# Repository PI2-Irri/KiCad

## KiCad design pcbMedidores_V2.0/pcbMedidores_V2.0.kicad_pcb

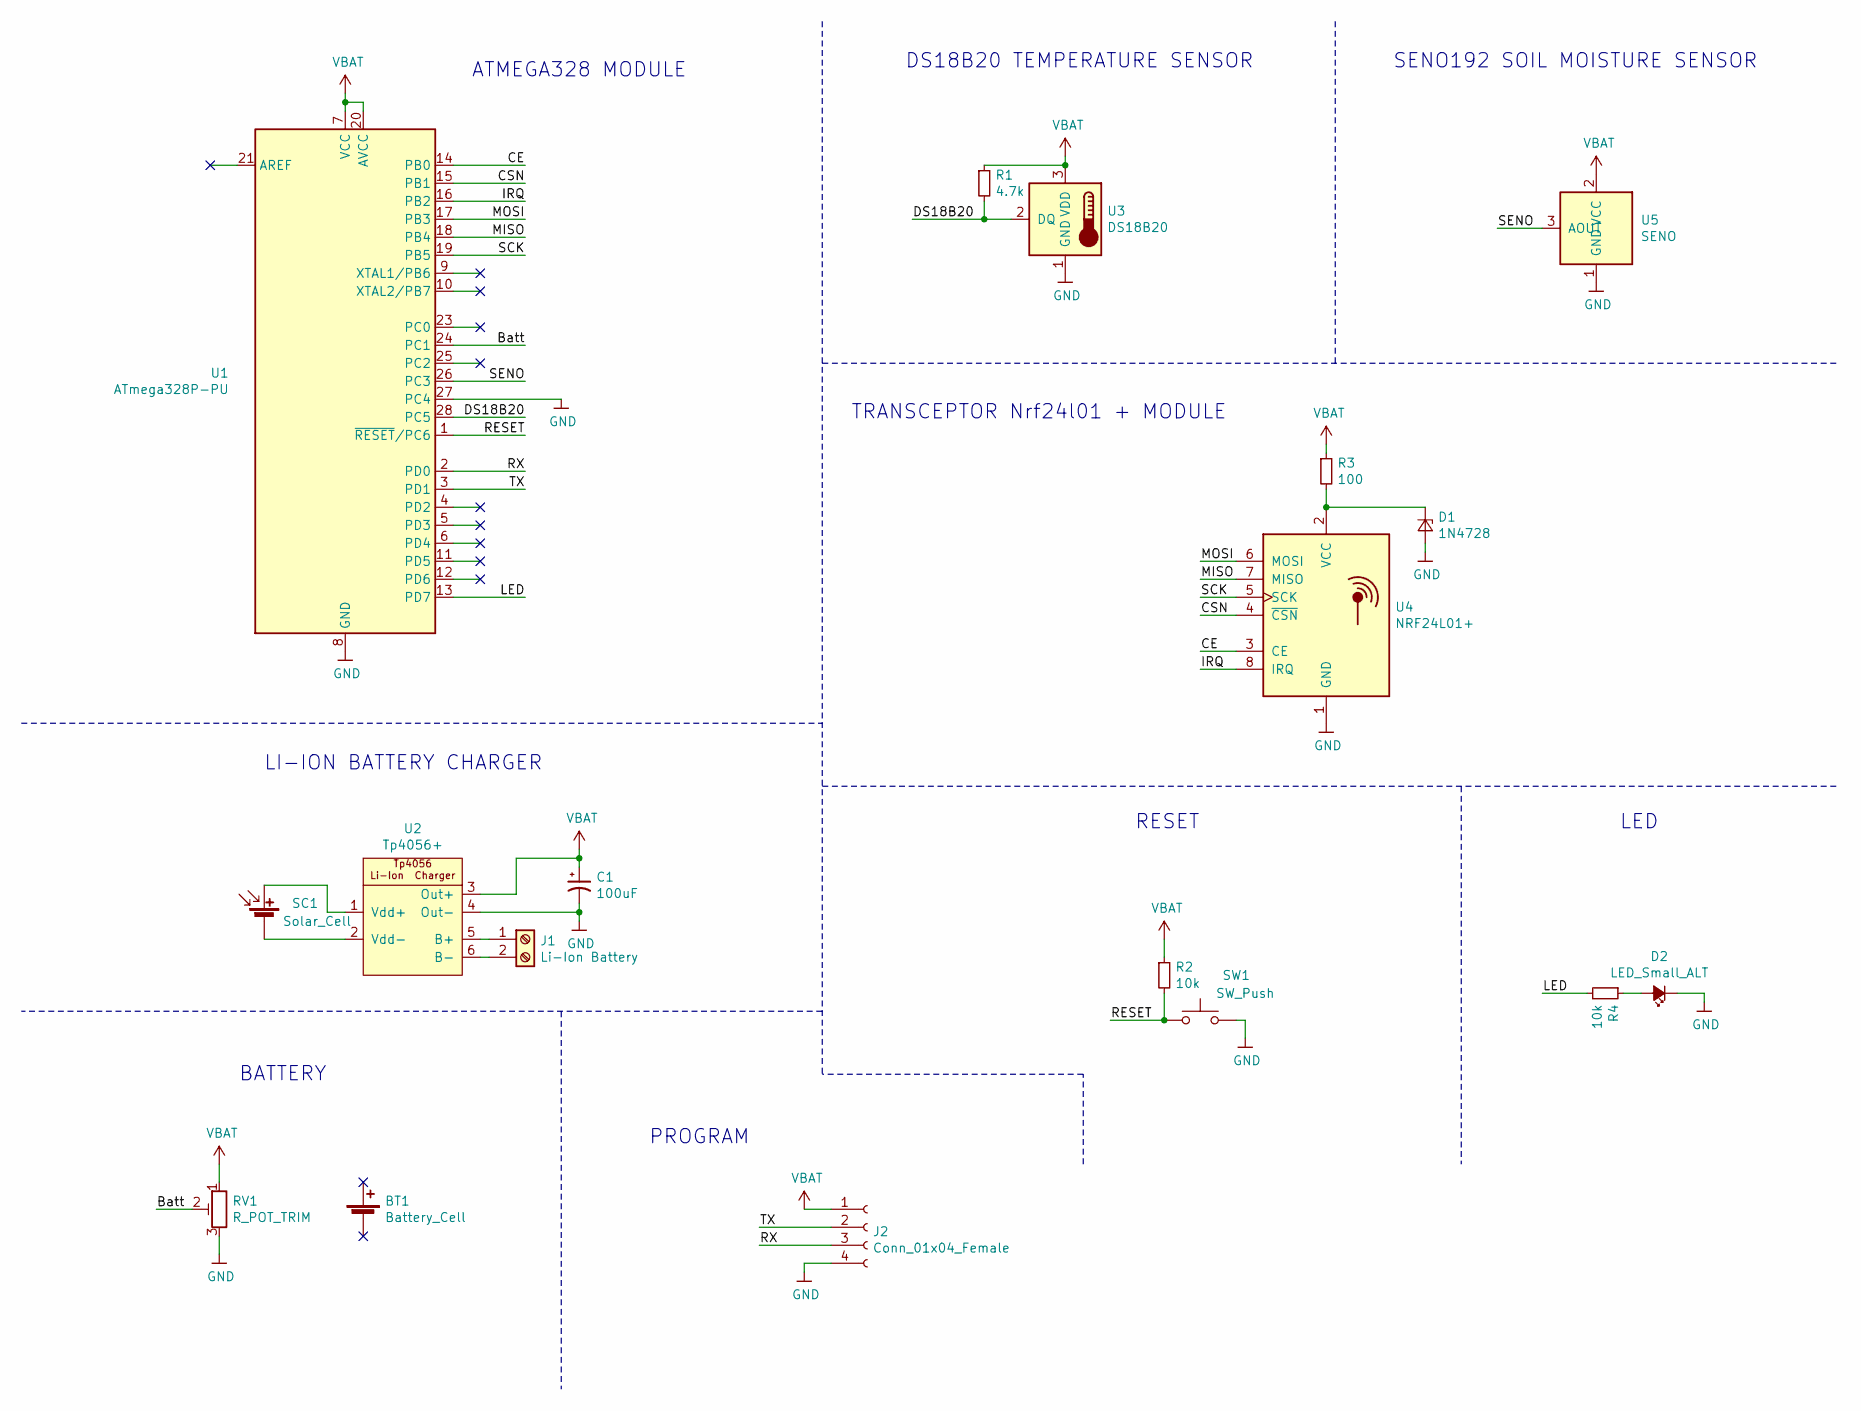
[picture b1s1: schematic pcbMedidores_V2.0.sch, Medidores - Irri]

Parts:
BT1: Battery_Cell; BatteryHolder
C1: 100uF; CP_Radial_D6.3mm_P2.50mm
D1: 1N4728; D_DO-41_SOD81_P10.16mm_Horizontal
D2: LED_Small_ALT; LED_Rectangular_W3.0mm_H2.0mm
J1: Li-Ion Battery; TerminalBlock_bornier-2_P5.08mm
J2: Conn_01x04_Female; PinHeader_1x04_P2.54mm_Vertical
R1: 4.7k; R_Axial_DIN0207_L6.3mm_D2.5mm_P7.62mm_Horizontal
R2, R4: 10k; R_Axial_DIN0207_L6.3mm_D2.5mm_P7.62mm_Horizontal
R3: 100; R_Axial_DIN0207_L6.3mm_D2.5mm_P7.62mm_Horizontal
RV1: R_POT_TRIM; Potentiometer_Bourns_3296W_Vertical
SC1: Solar_Cell; JST_XH_B2B-XH-A_1x02_P2.50mm_Vertical
SW1: SW_Push; SW_PUSH_6mm_H4.3mm
U1: ATmega328P-PU; DIP-28_W7.62mm_Socket_LongPads
U2: Tp4056+
U3: DS18B20; JST_XH_B3B-XH-A_1x03_P2.50mm_Vertical
U4: NRF24L01+; nRF24L01_Breakout
U5: SENO; PinHeader_1x03_P2.54mm_Vertical

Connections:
/Batt: RV1.2, U1.24 (PC1)
/CE: U1.14 (PB0), U4.3 (CE)
/CSN: U1.15 (PB1), U4.4 (~CSN)
/DS18B20: R1.2, U1.28 (PC5), U3.2 (DQ)
/IRQ: U1.16 (PB2), U4.8 (IRQ)
/LED: R4.2, U1.13 (PD7)
/MISO: U1.18 (PB4), U4.7 (MISO)
/MOSI: U1.17 (PB3), U4.6 (MOSI)
/RESET: R2.2, SW1.1, U1.1 (~RESET~/PC6)
/RX: J2.3, U1.2 (PD0)
/SCK: U1.19 (PB5), U4.5 (SCK)
/SENO: U1.26 (PC3), U5.3 (AOUT)
/TX: J2.2, U1.3 (PD1)
unnamed: D1.1 (K), R3.2, U4.2 (VCC)
unnamed: D2.2 (A), R4.1
unnamed: J1.1, U2.5 (B+)
unnamed: J1.2, U2.6 (B-)
unnamed: SC1.1 (+), U2.1 (Vdd+)
unnamed: SC1.2 (-), U2.2 (Vdd-)
VBUS: C1.1, J2.1, R1.1, R2.1, R3.1, RV1.1, U1.7 (VCC), U1.20 (AVCC), U2.3 (Out+), U3.3 (VDD), U5.2 (VCC)

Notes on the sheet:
LED
ATMEGA328 MODULE
DS18B20 TEMPERATURE SENSOR
SENO192 SOIL MOISTURE SENSOR
TRANSCEPTOR Nrf24l01 + MODULE
LI-ION BATTERY CHARGER
PROGRAM
RESET
BATTERY

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
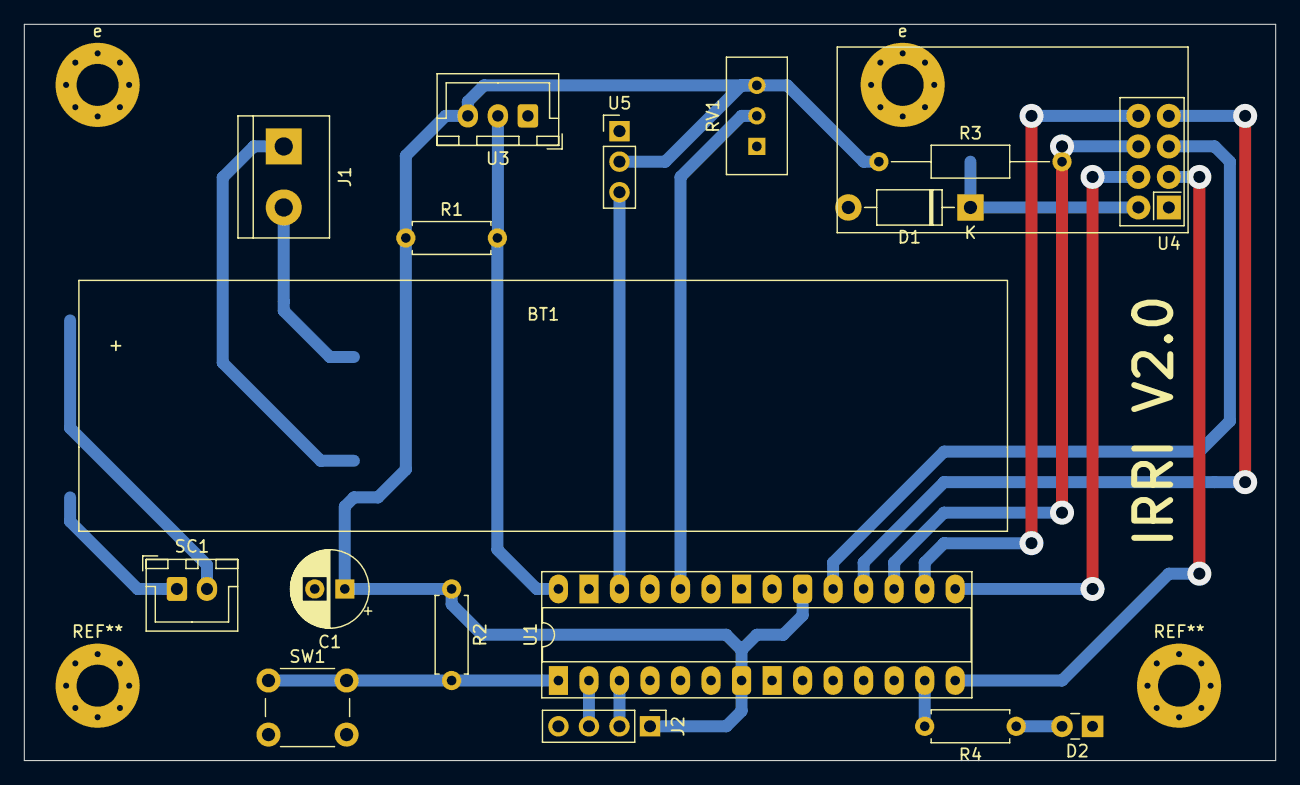
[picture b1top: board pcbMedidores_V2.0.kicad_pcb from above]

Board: 2 copper layers, 104.1 x 61.3 mm, 20 parts (1 on the bottom side), 21 nets.

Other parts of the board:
e: MountingHole_3.5mm_Pad_Via
e#2: MountingHole_3.5mm_Pad_Via

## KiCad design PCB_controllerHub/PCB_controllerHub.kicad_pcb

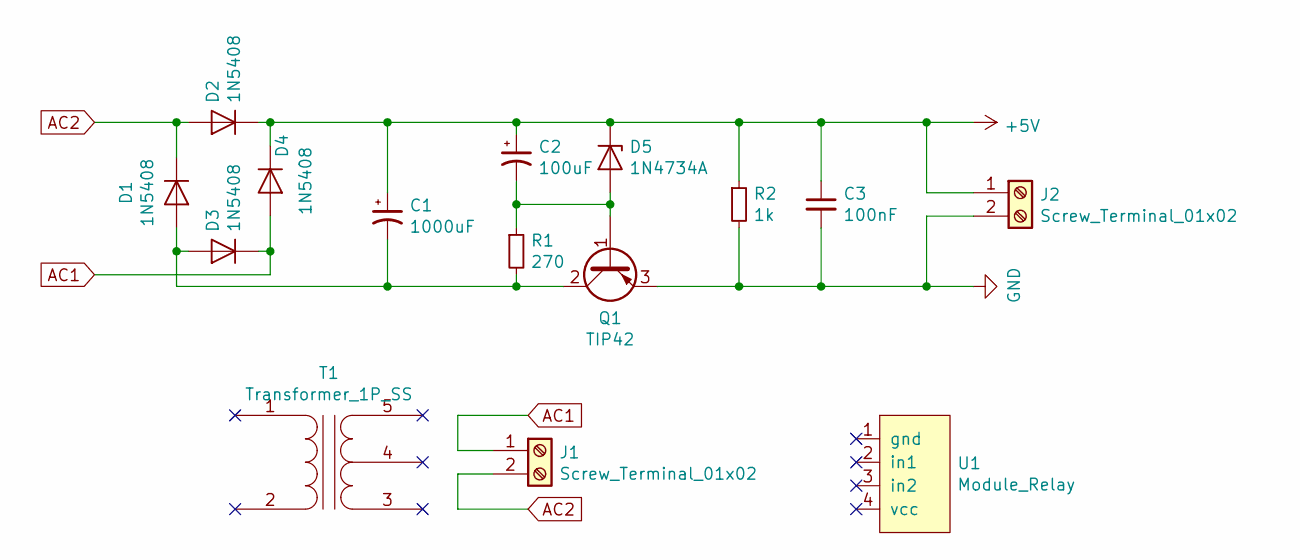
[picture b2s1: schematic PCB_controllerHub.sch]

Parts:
C1: 1000uF; CP_Radial_D10.0mm_P5.00mm
C2: 100uF; CP_Radial_D6.3mm_P2.50mm
C3: 100nF; C_Rect_L7.2mm_W2.5mm_P5.00mm_FKS2_FKP2_MKS2_MKP2
D1, D2, D3, D4: 1N5408; D_DO-201AD_P15.24mm_Horizontal
D5: 1N4734A; D_DO-41_SOD81_P10.16mm_Horizontal
J1, J2: Screw_Terminal_01x02; TerminalBlock_bornier-2_P5.08mm
Q1: TIP42; TO-220-3_Vertical
R1: 270; R_Axial_DIN0309_L9.0mm_D3.2mm_P12.70mm_Horizontal
R2: 1k; R_Axial_DIN0207_L6.3mm_D2.5mm_P10.16mm_Horizontal
T1: Transformer_1P_SS; Trafo_1A_6V
U1: Module_Relay; Module_relay

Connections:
+5V: C1.1, C2.1, C3.1, D2.1 (K), D4.1 (K), D5.1 (K), J2.1, R2.1
AC1: D3.1 (K), D4.2 (A), J1.1
AC2: D1.1 (K), D2.2 (A), J1.2
GND: C3.2, J2.2, Q1.3 (E), R2.2
unnamed: C1.2, D1.2 (A), D3.2 (A), Q1.2 (C), R1.2
unnamed: C2.2, D5.2 (A), Q1.1 (B), R1.1

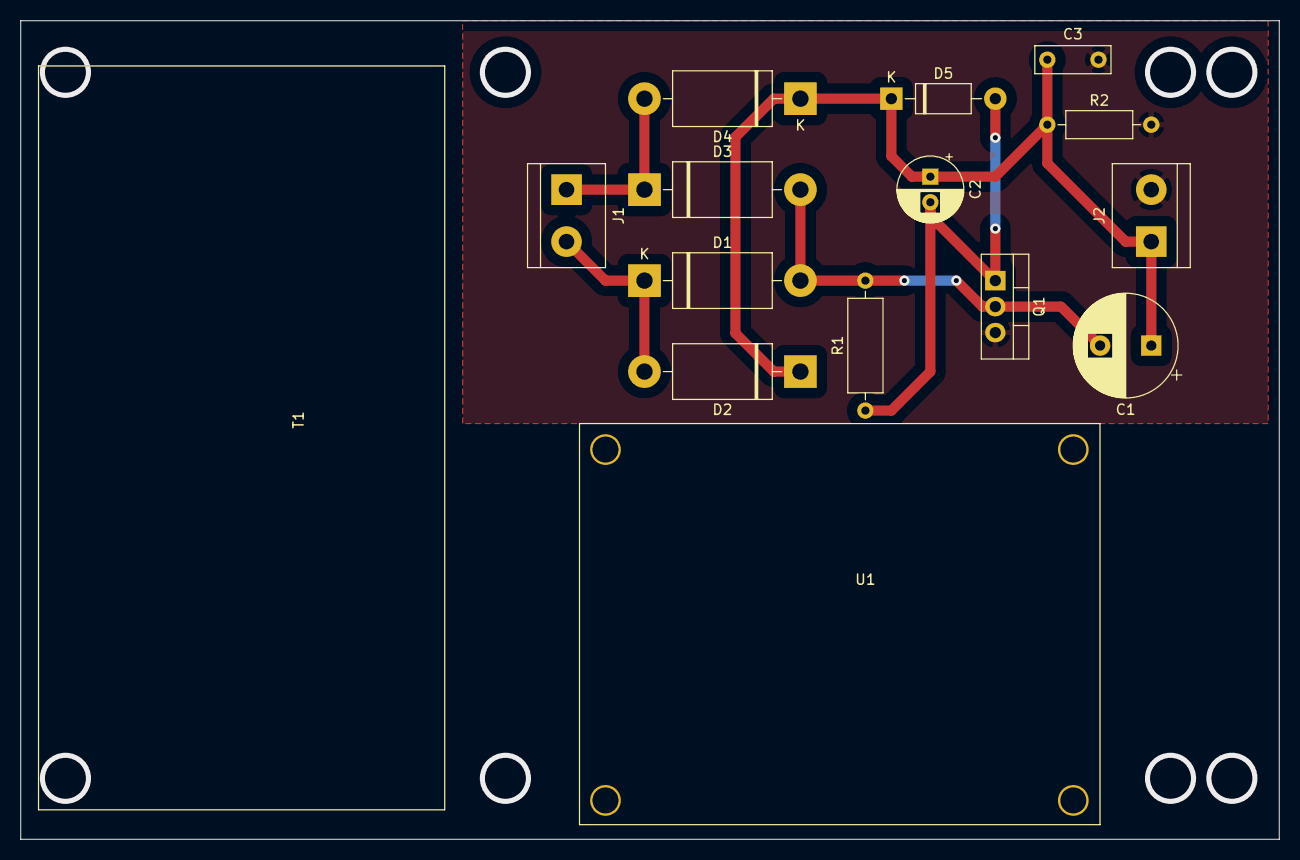
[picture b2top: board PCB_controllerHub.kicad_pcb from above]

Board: 2 copper layers, 123.0 x 80.0 mm, 15 parts (0 on the bottom side), 6 nets.

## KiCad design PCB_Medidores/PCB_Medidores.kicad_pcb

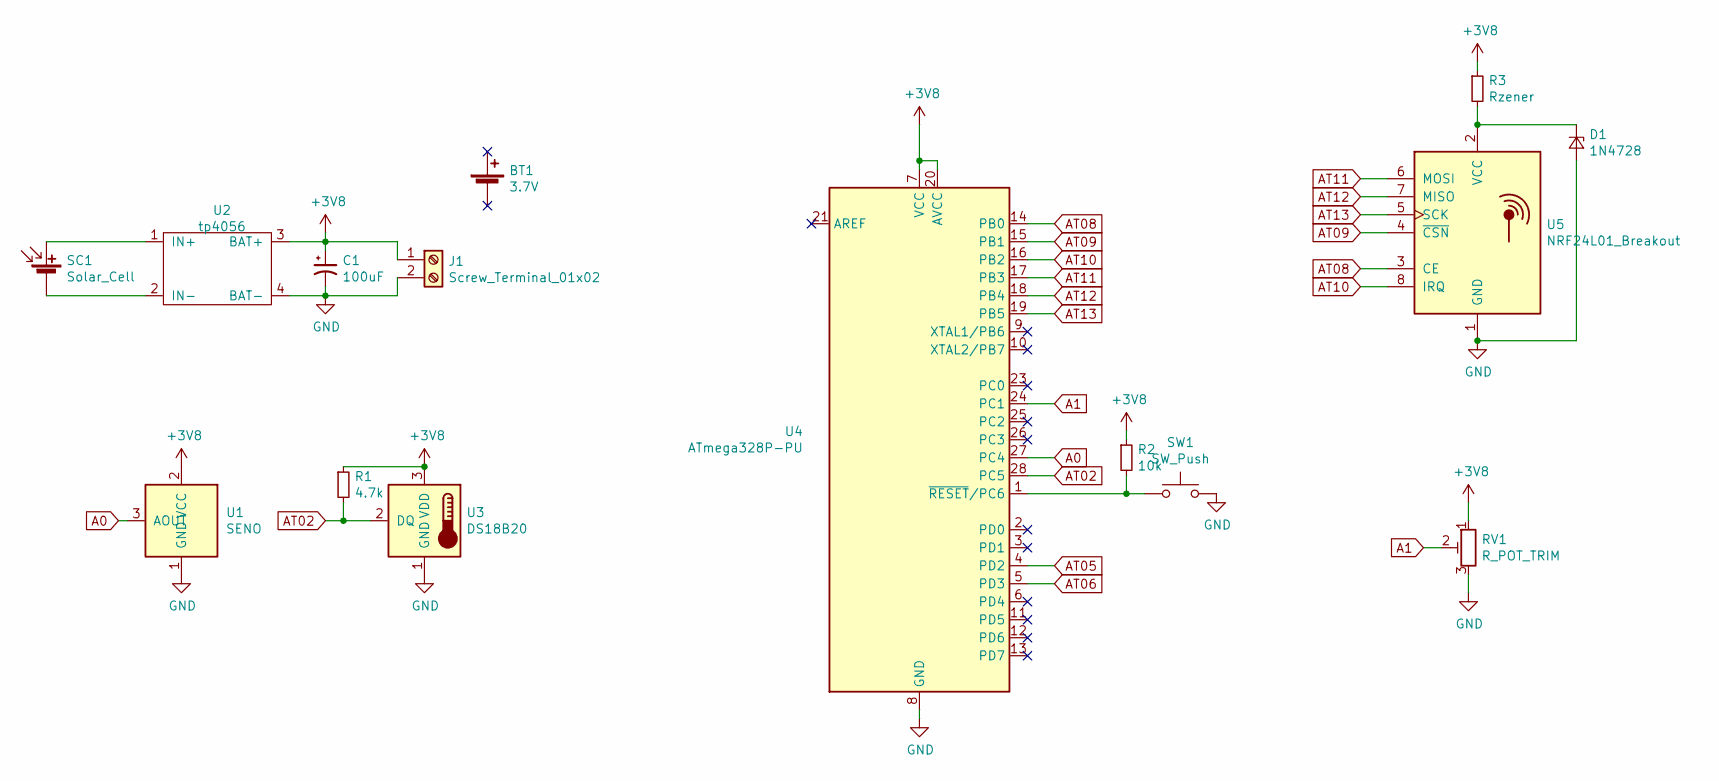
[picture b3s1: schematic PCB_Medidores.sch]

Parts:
BT1: 3.7V; BatteryHolder
C1: 100uF; CP_Radial_D6.3mm_P2.50mm
D1: 1N4728; D_DO-41_SOD81_P10.16mm_Horizontal
J1: Screw_Terminal_01x02; TerminalBlock_bornier-2_P5.08mm
R1: 4.7k; R_Axial_DIN0207_L6.3mm_D2.5mm_P10.16mm_Horizontal
R2: 10k; R_Axial_DIN0207_L6.3mm_D2.5mm_P10.16mm_Horizontal
R3: Rzener; R_Axial_DIN0207_L6.3mm_D2.5mm_P15.24mm_Horizontal
RV1: R_POT_TRIM; Potentiometer_Bourns_3296W_Vertical
SC1: Solar_Cell; JST_XH_B2B-XH-A_1x02_P2.50mm_Vertical
SW1: SW_Push; SW_PUSH_6mm_H4.3mm
U1: SENO; PinHeader_1x03_P2.54mm_Vertical
U2: tp4056
U3: DS18B20; JST_XH_B3B-XH-A_1x03_P2.50mm_Vertical
U4: ATmega328P-PU; DIP-28_W7.62mm
U5: NRF24L01_Breakout; nRF24L01_Breakout

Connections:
+3V8: C1.1, J1.1, R1.1, R2.1, R3.1, RV1.1, U1.2 (VCC), U2.3 (BAT+), U3.3 (VDD), U4.7 (VCC), U4.20 (AVCC)
A0: U1.3 (AOUT), U4.27 (PC4)
A1: RV1.2, U4.24 (PC1)
AT02: R1.2, U3.2 (DQ), U4.28 (PC5)
AT05: U4.4 (PD2)
AT06: U4.5 (PD3)
AT08: U4.14 (PB0), U5.3 (CE)
AT09: U4.15 (PB1), U5.4 (~CSN)
AT10: U4.16 (PB2), U5.8 (IRQ)
AT11: U4.17 (PB3), U5.6 (MOSI)
AT12: U4.18 (PB4), U5.7 (MISO)
AT13: U4.19 (PB5), U5.5 (SCK)
GND: C1.2, D1.2 (A), J1.2, RV1.3, SW1.2, U1.1 (GND), U2.4 (BAT-), U3.1 (GND), U4.8 (GND), U4.22 (GND), U5.1 (GND)
unnamed: D1.1 (K), R3.2, U5.2 (VCC)
unnamed: R2.2, SW1.1, U4.1 (~RESET~/PC6)
unnamed: SC1.1 (+), U2.1 (IN+)
unnamed: SC1.2 (-), U2.2 (IN-)

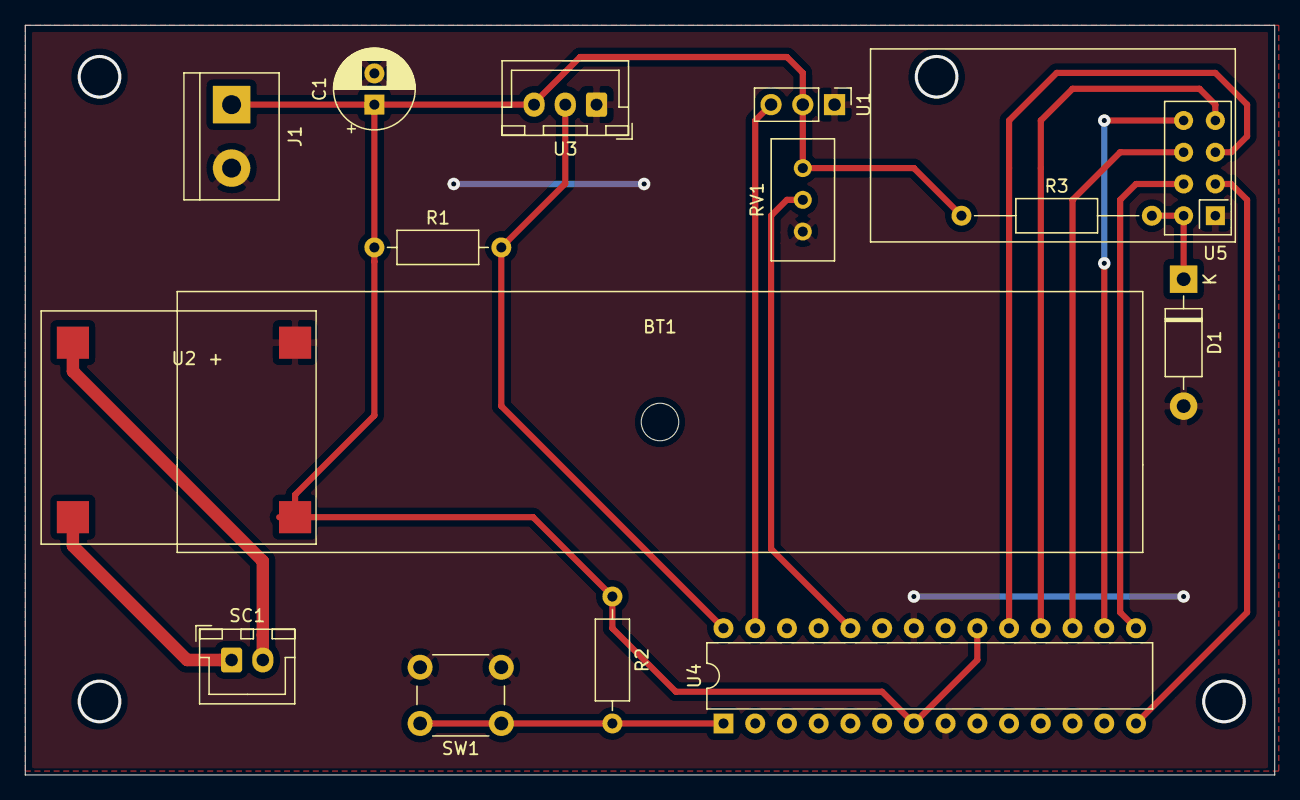
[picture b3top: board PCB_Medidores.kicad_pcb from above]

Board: 2 copper layers, 100.0 x 60.0 mm, 15 parts (0 on the bottom side), 15 nets.

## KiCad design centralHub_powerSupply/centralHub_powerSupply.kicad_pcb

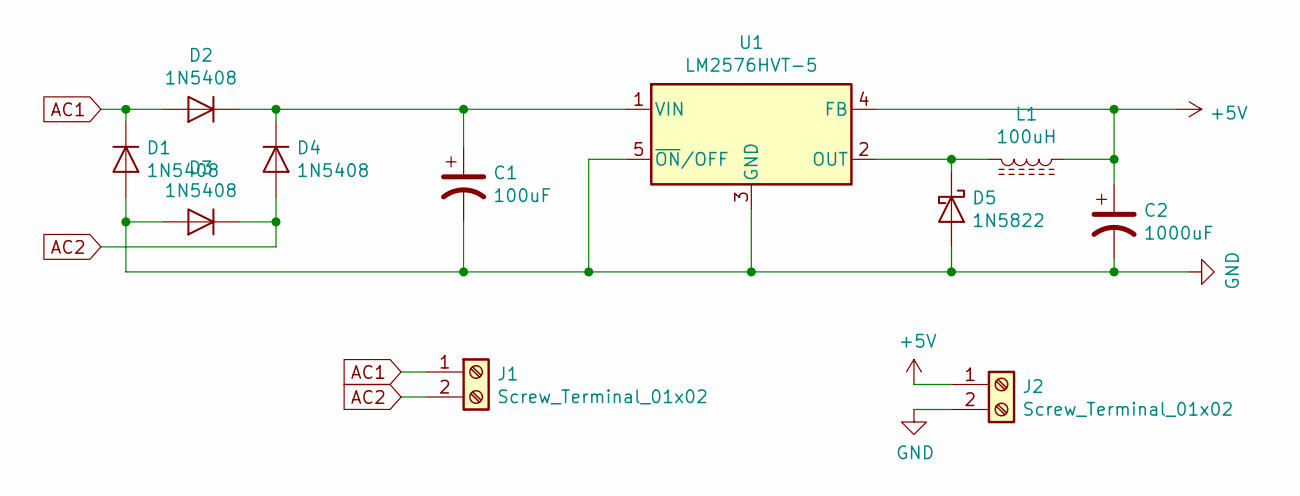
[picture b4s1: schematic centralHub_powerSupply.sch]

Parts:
C1: 100uF; CP_Radial_D6.3mm_P2.50mm
C2: 1000uF; CP_Radial_D10.0mm_P5.00mm
D1, D2, D3, D4: 1N5408; D_DO-201AD_P15.24mm_Horizontal
D5: 1N5822; D_DO-201AD_P15.24mm_Horizontal
J1, J2: Screw_Terminal_01x02; TerminalBlock_bornier-2_P5.08mm
L1: 100uH; L_Toroid_Vertical_L16.4mm_W7.6mm_P6.60mm_Vishay_TJ3
U1: LM2576HVT-5; TO-220-5_P3.4x3.7mm_StaggerOdd_Lead3.8mm_Vertical

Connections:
+5V: C2.1, J2.1, L1.2, U1.4 (FB)
AC1: D1.1 (K), D2.2 (A), J1.1
AC2: D3.1 (K), D4.2 (A), J1.2
GND: C1.2, C2.2, D1.2 (A), D3.2 (A), D5.2 (A), J2.2, U1.3 (GND), U1.5 (~ON~/OFF)
unnamed: C1.1, D2.1 (K), D4.1 (K), U1.1 (VIN)
unnamed: D5.1 (K), L1.1, U1.2 (OUT)

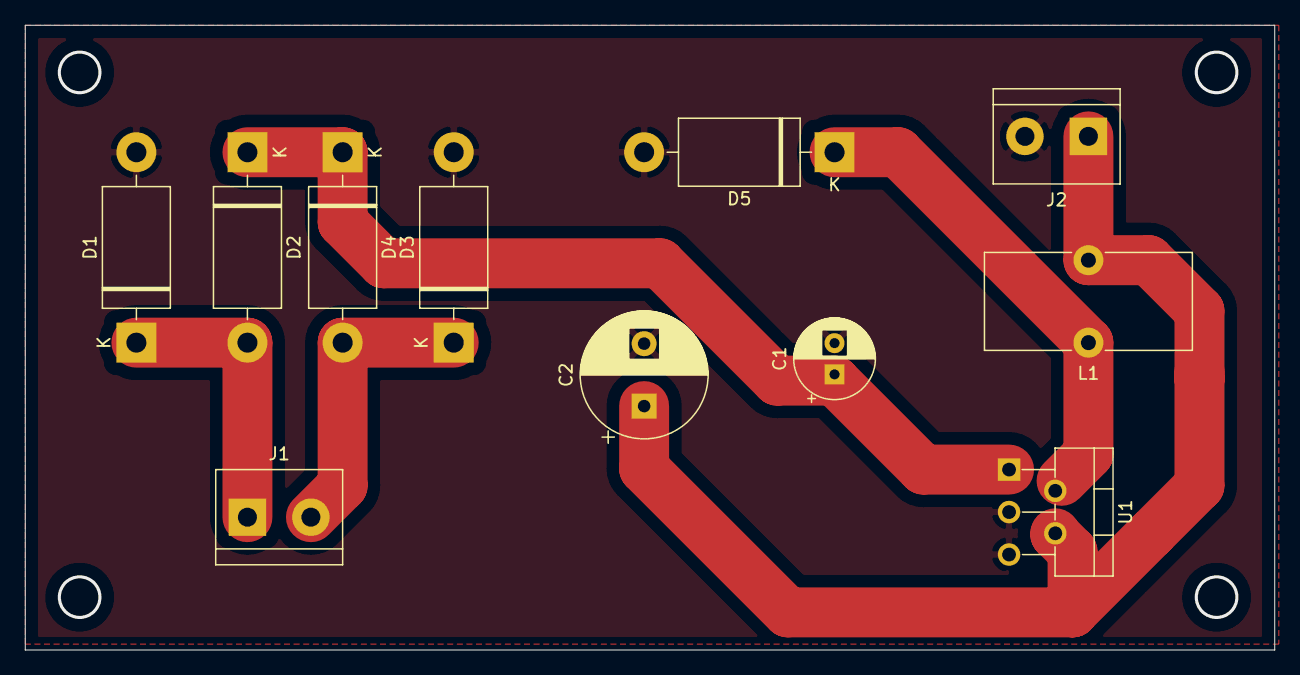
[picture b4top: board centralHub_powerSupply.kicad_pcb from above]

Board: 2 copper layers, 100.0 x 50.0 mm, 11 parts (0 on the bottom side), 6 nets.

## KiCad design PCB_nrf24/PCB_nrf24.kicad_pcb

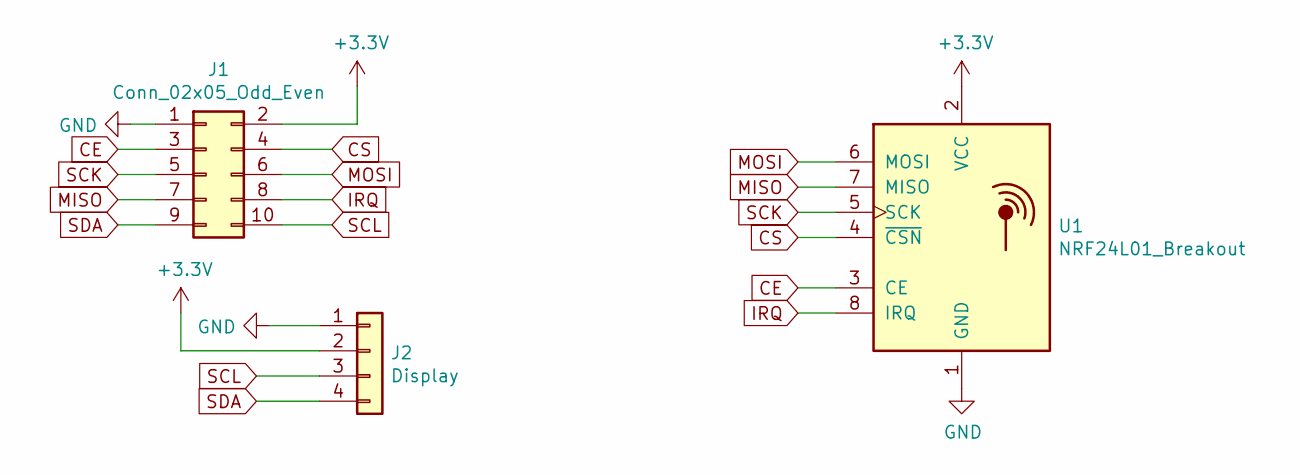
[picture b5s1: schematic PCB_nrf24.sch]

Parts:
J1: Conn_02x05_Odd_Even; IDC-Header_2x05_P2.54mm_Vertical
J2: Display; PinSocket_1x04_P2.54mm_Vertical
U1: NRF24L01_Breakout; nRF24L01_Breakout

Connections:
+3V3: J1.2, J2.2, U1.2 (VCC)
CE: J1.3, U1.3 (CE)
CS: J1.4, U1.4 (~CSN)
GND: J1.1, J2.1, U1.1 (GND)
IRQ: J1.8, U1.8 (IRQ)
MISO: J1.7, U1.7 (MISO)
MOSI: J1.6, U1.6 (MOSI)
SCK: J1.5, U1.5 (SCK)
SCL: J1.10, J2.3
SDA: J1.9, J2.4

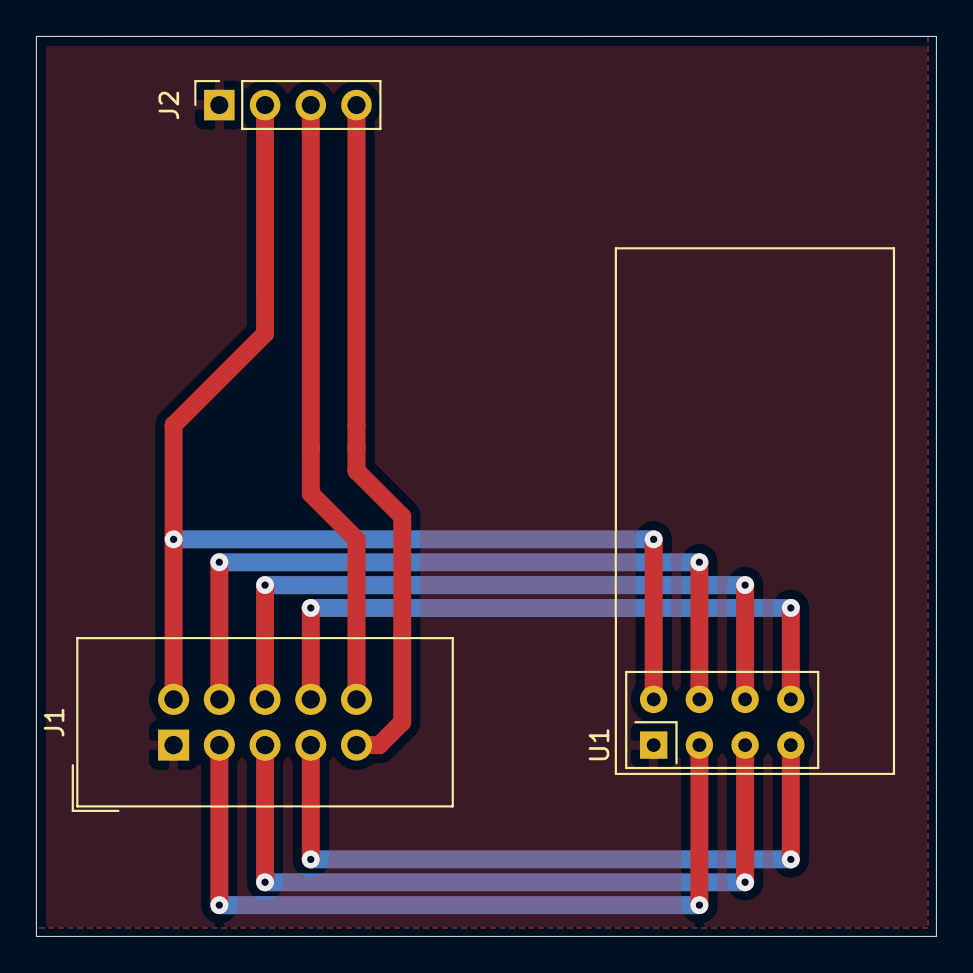
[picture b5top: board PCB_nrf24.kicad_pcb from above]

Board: 2 copper layers, 50.0 x 50.0 mm, 3 parts (0 on the bottom side), 10 nets.

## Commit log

2019-10-24 [Schematic]
    Schematic dos módulos medidores
2019-10-24 [PCB]
2019-10-25 Initial Schematics for Central Hub & Controllers
2019-10-28 [Central e Atuadores]
2019-10-30 GOOUUU-ESP32 Symbol & FootPrint & PCB_ESP32 Draft
2019-10-31 [Power Supply PCBS DONE!]
2019-10-31 Fix Commit - Upload remaining files
2019-11-01 [PCB Medidores e Correção]
2019-11-02 [PCB ESP32 e NRF]
2019-11-02 PCB Medidores - Minor Corrections
2019-11-05 Fix minor error in ControllerHub Power Supply & Git files cleanup
2019-11-18 [PCB medidores V2.0]
    -Correçao da PCB e melhorias
2019-11-19 [Minor correction]
